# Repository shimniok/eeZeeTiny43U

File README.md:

Breadboard breakout board for ATtiny43U

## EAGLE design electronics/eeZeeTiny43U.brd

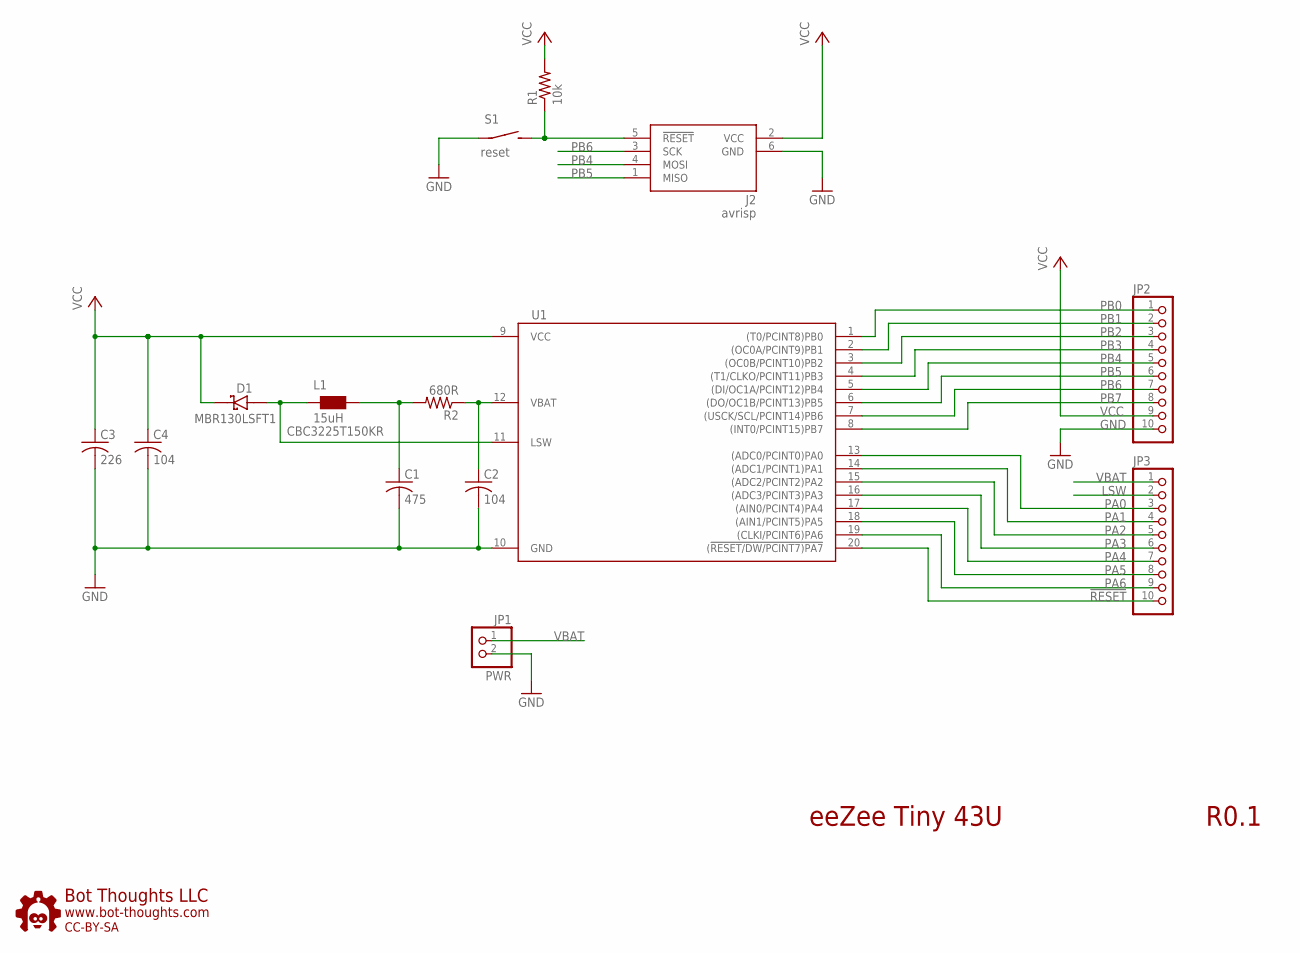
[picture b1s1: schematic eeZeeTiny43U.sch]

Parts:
C1: 475; 0603; PARTNO 0603YC104KAT2A
C2, C4: 104; 0603; PARTNO 0603YC104KAT2A
C3: 226; 1206; PARTNO MCTT21X106M6R3CT
D1: MBR130LSFT1; SOD123FL
J2: avrisp; CON6P2R
JP1: PWR; 1X02-S
JP2, JP3: PINHD-1X10_2.54-S; 1X10-S
L1: 15uH; 1210; PARTNO CBC3225T150KR
R1: 10k; 0603; PARTNO ERJ-3GEYJ103V
R2: 680R; 0603; PARTNO ERJ-3GEYJ103V
S1: reset; 6MMTACTILE_RECT
U1: ATTINY43U-SU; SOIC20
U$1: BTLOGO-LOGO-MD; BTLOGOM

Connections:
!RESET: J2.5 (!RESET), JP3.10, R1.1, S1.P$2 (S), U1.20 ((!RESET/DW/PCINT7)PA7)
GND: C1.2 (-), C2.2 (-), C3.2 (-), C4.2 (-), J2.6 (GND), JP1.2, JP2.10, S1.P$1, U1.10 (GND)
LSW: D1.A, JP3.2, L1.1, U1.11 (LSW)
PA0: JP3.3, U1.13 ((ADC0/PCINT0)PA0)
PA1: JP3.4, U1.14 ((ADC1/PCINT1)PA1)
PA2: JP3.5, U1.15 ((ADC2/PCINT2)PA2)
PA3: JP3.6, U1.16 ((ADC3/PCINT3)PA3)
PA4: JP3.7, U1.17 ((AIN0/PCINT4)PA4)
PA5: JP3.8, U1.18 ((AIN1/PCINT5)PA5)
PA6: JP3.9, U1.19 ((CLKI/PCINT6)PA6)
PB0: JP2.1, U1.1 ((T0/PCINT8)PB0)
PB1: JP2.2, U1.2 ((OC0A/PCINT9)PB1)
PB2: JP2.3, U1.3 ((OC0B/PCINT10)PB2)
PB3: JP2.4, U1.4 ((T1/CLKO/PCINT11)PB3)
PB4: J2.4 (MOSI), JP2.5, U1.5 ((DI/OC1A/PCINT12)PB4)
PB5: J2.1 (MISO), JP2.6, U1.6 ((DO/OC1B/PCINT13)PB5)
PB6: J2.3 (SCK), JP2.7, U1.7 ((USCK/SCL/PCINT14)PB6)
PB7: JP2.8, U1.8 ((INT0/PCINT15)PB7)
VBAT: C2.1 (+), JP1.1, JP3.1, R2.1, U1.12 (VBAT)
VBAT1: C1.1 (+), L1.2, R2.2
VCC: C3.1 (+), C4.1 (+), D1.C, J2.2 (VCC), JP2.9, R1.2, U1.9 (VCC)

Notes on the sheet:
eeZee Tiny 43U
R0.1

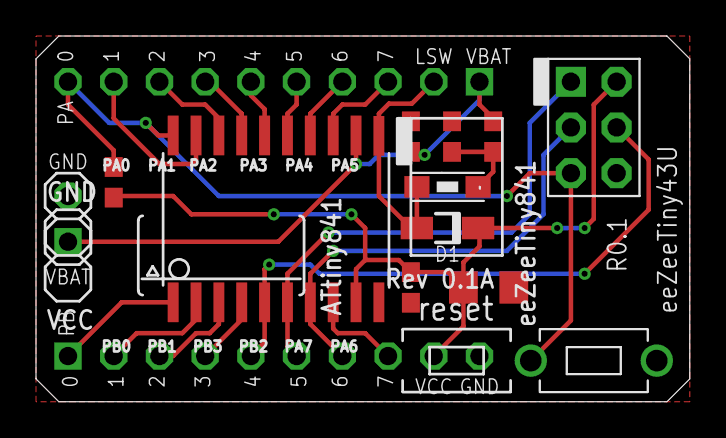
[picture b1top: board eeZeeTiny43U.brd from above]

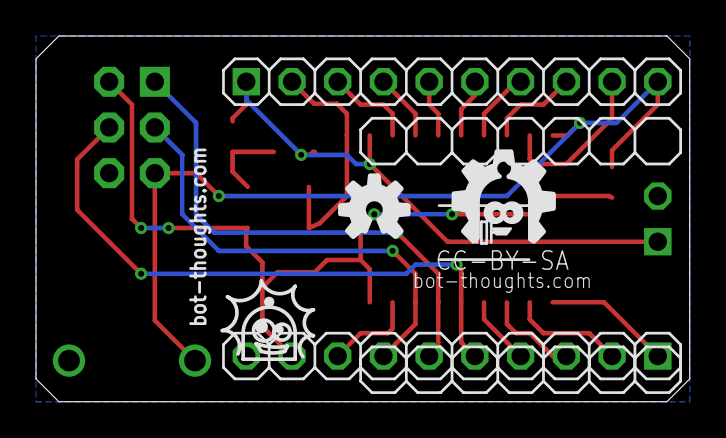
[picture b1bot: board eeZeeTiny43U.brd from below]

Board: 2 copper layers, 36.3 x 20.3 mm, 15 parts (3 on the bottom side), 21 nets.

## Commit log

2018-01-17 initial release
2018-01-17 added readme
2018-01-17 moved gitignore
2021-02-10 don't recall

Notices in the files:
electronics/eeZeeTiny43U.brd:
CC-BY-SA
parts and their libraries:
wuerth-elektronik: Copyright: Würth Elektronik eiSos
